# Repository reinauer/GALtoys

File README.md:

# GAL toys

This repostitory contains some random GAL toys.

## GALex

Mount a socket on top and a PLCC plug on the bottom, or just a socket on the
bottom. This board exposes all GAL signals on pin headers surrounding the chip.

## GALpowerup

GAL interposer that connects pin 1 to VCC and 8, 15 and 22 to GND. Mount a
socket on top and a PLCC plug on the bottom.

## JEDi

JED interpreter for converting non-standard JED files to standard JEDEC format.
See [JEDi/README.md](JEDi/README.md).

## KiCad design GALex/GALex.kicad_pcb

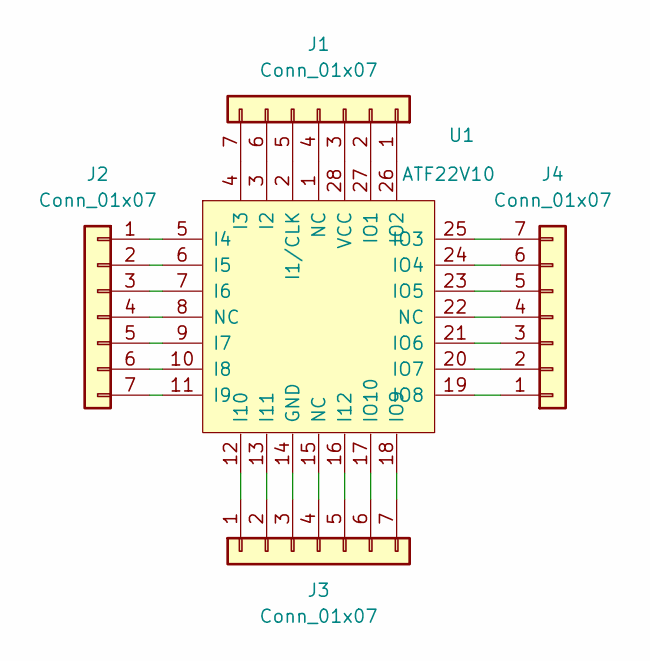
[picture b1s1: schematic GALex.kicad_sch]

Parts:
J1, J2, J3, J4: Conn_01x07; PinHeader_1x07_P2.54mm_Vertical
U1: ATF22V10; APW9323

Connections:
unnamed: J2.1, U1.5 (I4)
unnamed: J2.2, U1.6 (I5)
unnamed: J2.3, U1.7 (I6)
unnamed: J2.4, U1.8 (NC)
unnamed: J2.5, U1.9 (I7)
unnamed: J2.6, U1.10 (I8)
unnamed: J2.7, U1.11 (I9)
unnamed: J3.1, U1.12 (I10)
unnamed: J3.2, U1.13 (I11)
unnamed: J3.3, U1.14 (GND)
unnamed: J3.4, U1.15 (NC)
unnamed: J3.5, U1.16 (I12)
unnamed: J3.6, U1.17 (IO10)
unnamed: J3.7, U1.18 (IO9)
unnamed: J4.1, U1.19 (IO8)
unnamed: J4.2, U1.20 (IO7)
unnamed: J4.3, U1.21 (IO6)
unnamed: J4.4, U1.22 (NC)
unnamed: J4.5, U1.23 (IO5)
unnamed: J4.6, U1.24 (IO4)
unnamed: J4.7, U1.25 (IO3)
unnamed: J1.4, U1.1 (NC)
unnamed: J1.5, U1.2 (I1/CLK)
unnamed: J1.6, U1.3 (I2)
unnamed: J1.7, U1.4 (I3)
unnamed: J1.1, U1.26 (IO2)
unnamed: J1.2, U1.27 (IO1)
unnamed: J1.3, U1.28 (VCC)

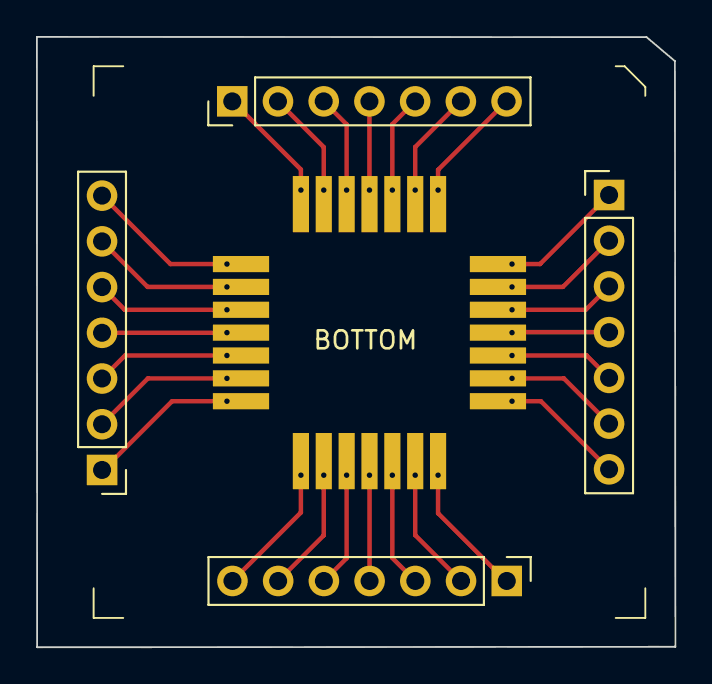
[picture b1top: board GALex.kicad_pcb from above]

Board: 2 copper layers, 35.5 x 33.9 mm, 5 parts (0 on the bottom side), 28 nets.

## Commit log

2024-08-28 Add some pictures
2024-08-28 KiCAD wanted to change this
2024-08-28 PNG not JPG
2024-08-28 Fix image path
2025-12-27 Add JED file fixer: JEDi
2026-03-09 JEDi: terminate final C record before ETX
    JEDi writes the fuse checksum record as:
    *Cxxxx\r\n<ETX>yyyy
    This leaves the final JEDEC field unterminated. Some tools accept that,
    but strict parsers reject the file as corrupt before parsing the fuse
    map. GALEP5 reports this as "Line 0 - The file is corrupt or wrong."
    Emit the missing '*' before ETX so the final checksum record is framed
2026-03-15 jedi: handle universal programmer JED files for GALEP
    The 3660 GAL dumps are neither Wellon nor G540 files. They are
    STX-framed "universal programmer" JEDs with device-specific L record
    widths, no QF record, and checksums that trip GALEP5 with "Fuse CRC!".
    The existing fallback path treated these files as an unknown format and
    rewrote them into the minipro-style dialect. That flattened the fuse
    map into 32-bit rows, dropped the original row layout, and produced
